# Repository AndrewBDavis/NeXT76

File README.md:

NeXT76 Left-Handed Alps Keyboard
=====================
The primary goal of this project was create as PCB and accompanying layered acrylic case to exclusively support NeXT non-adb keycaps and Alps Electric SKCM/SKCL switches.

Supported Layouts
---------------
This keyboard only supports a [modifed NeXT non-adb layout](https://tinyurl.com/mrxz3pk3) with no volume, brightness or arrow keys and a numpad that is moved to the left of the alphanumericals. Shift key leds are supported.

Numpad Layouts supported:  
| 1u | 1u | 1u | 1u |  | 1u | 1u | 1u | 1u |  | 1u | 1u | 1u | 1u |
|----|----|----|----|--|----|----|----|----|--|----|----|----|----|
| 1u | 1u | 1u | 1u |  | 1u | 1u | 1u | 1u |  | 1u | 1u | 1u | 1u |
| 1u | 1u | 1u | 1u |  | 1u | 1u | 1u | 1u |  | 1u | 1u | 1u | 1u |
| 1u | 1u | 1u | 2u |  | 2u | 1u | 1u | 1u |  | 1u | 1u | 1u | 1u |
| 2u | 2u | 1u | 2u |  | 2u | 1u | 2u | 2u |  | 1u | 2u | 2u | 1u |  

(Some layouts not shown explicitly)

BOM for Alps76 keyboard                                                  
------------------
| REF:  | VALUE:     | FOOTPRINT:           | COMPONENT            |
|------ | ---------- | -------------------- | -------------------- |  
| C1    | 22p        | C_0805               |                      |
| C2    | 22p        | C_0805               |                      |     
| C3    | 1u         | C_0805               |                      |
| C4    | 4.7u       | C_0805               |                      |
| C5    | 0.1u       | C_0805               |                      |
| C6    | 0.1u       | C_0805               |                      |
| C7    | 0.1u       | C_0805               |                      |
| C8    | 0.1u       | C_0805               |                      |
| J1    | USB_mini_B | USB_miniB_hirose_5S8 | UX60SC-MB-5S8 Hirose |
| R1    | 22         | R_0805               |                      |
| R2    | 22         | R_0805               |                      |
| R3    | 10K        | R_0805               |                      |
| R4    | 10K        | R_0805               |                      |
| R5    | 1K         | R_0805               |                      |
| R6    | 1K         | R_0805               |                      |
| R7    | 1K         | R_0805               |                      |
| SW1   | SW_PUSH    | Custom               | TE 1825966-1         |
| U1    | ATMEGA32U4 | QFP44                | ATMega32u4-AU        | 
| X1    | CRYSTAL    | FA-238               | 16MHz, 12PF          |
| D(78) | DIODE      | SOD-123              | 1N4148               |
| LED(3)| LED        | LED_D3.0mm           | 3mm Round Top LED    |

Revisions
-------------
V0.0: 	Prototype  
V1.0: 	Initial Release  
&emsp;&emsp;&nbsp;&nbsp;Cleaned up trace routing  
&emsp;&emsp;&nbsp;&nbsp;Added more numpad configurations  
V1.1: 	Added second numpad LED location option  
V1.2: 	Updated diode footprints,

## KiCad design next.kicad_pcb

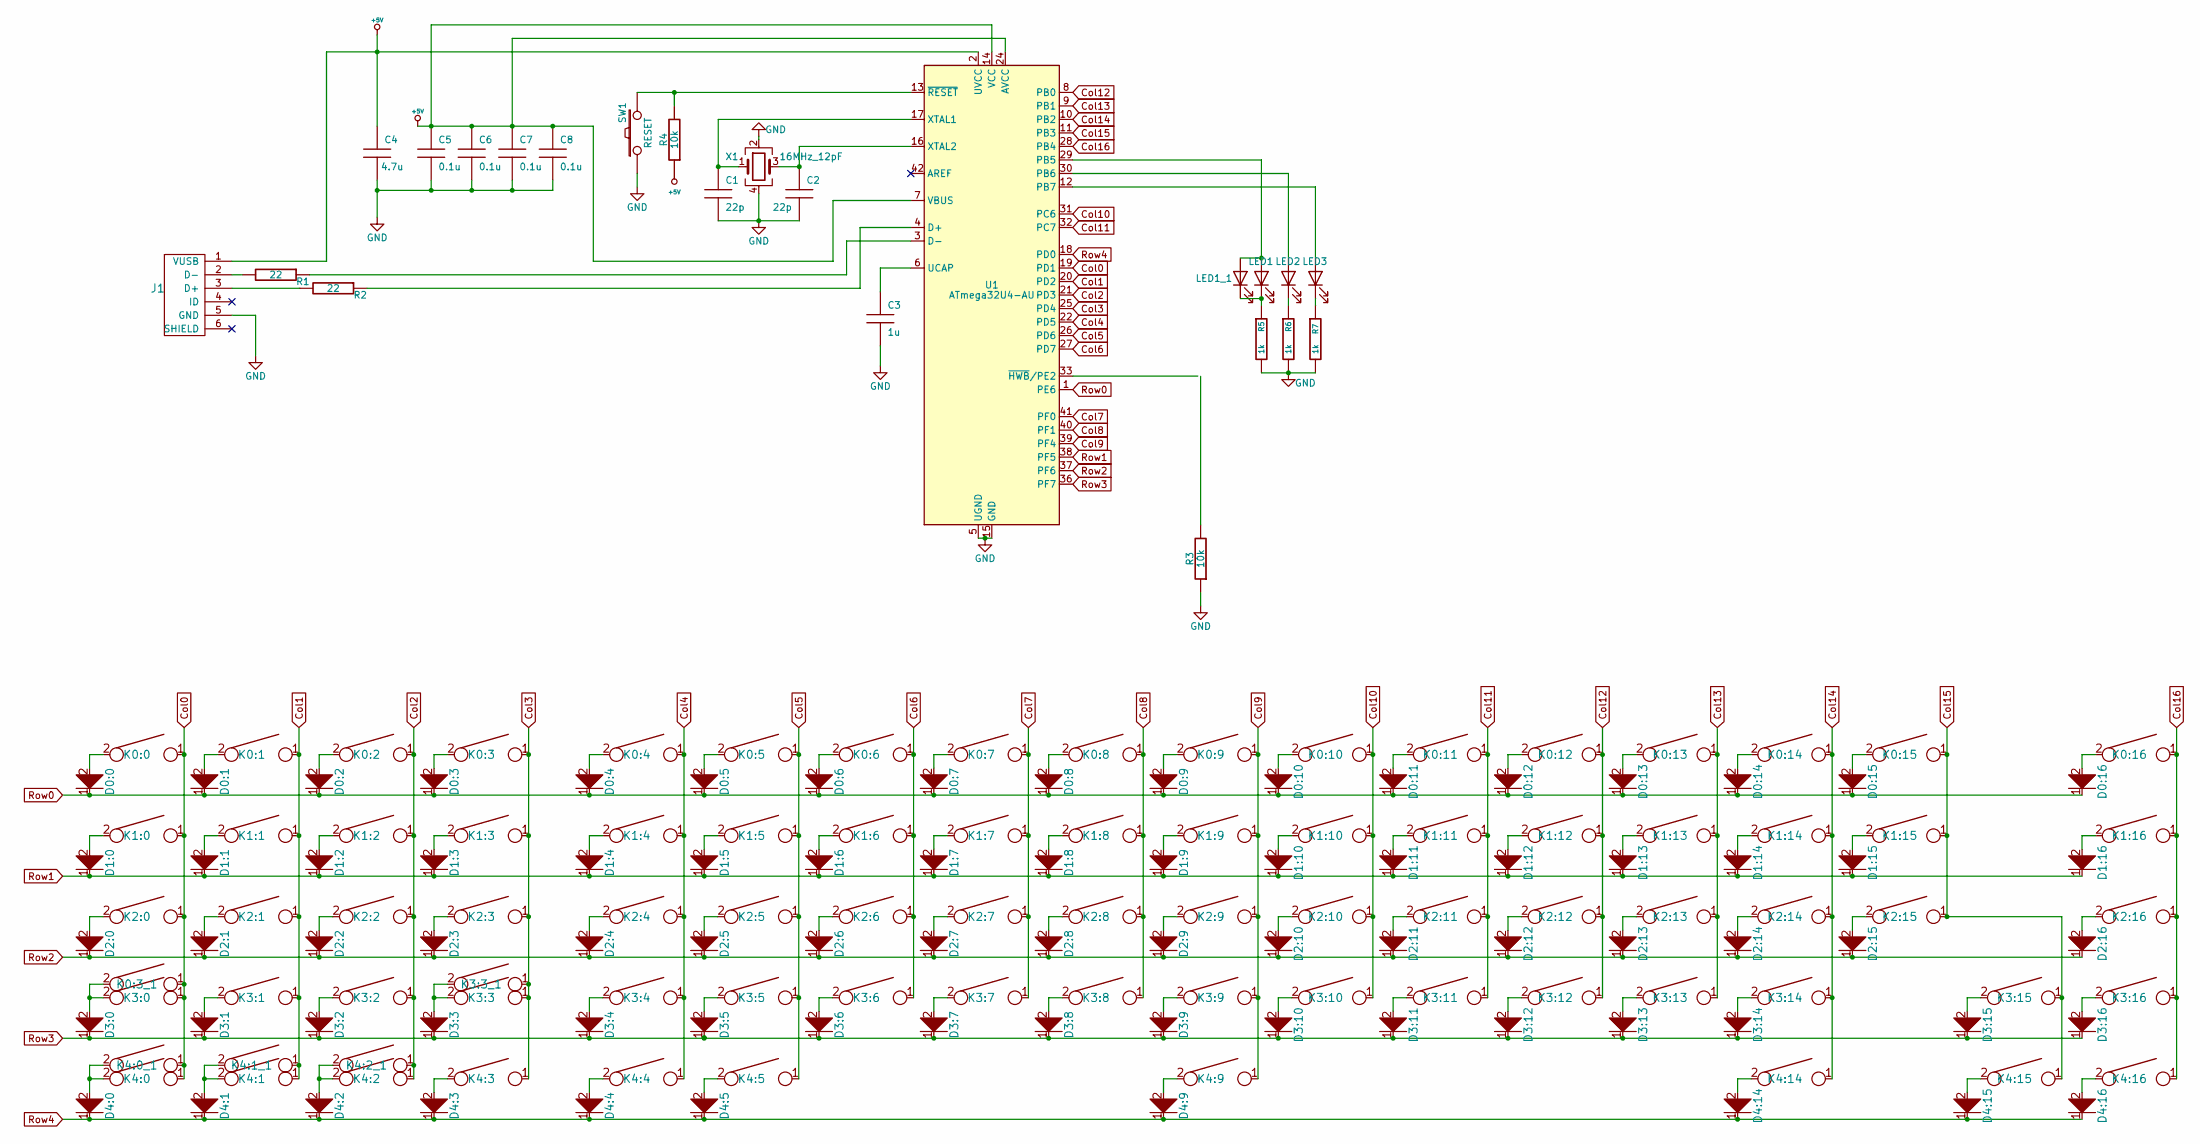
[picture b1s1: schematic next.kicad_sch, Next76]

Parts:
C1, C2: 22p; C_0805_2012Metric
C3: 1u; C_0805_2012Metric
C4: 4.7u; C_0805_2012Metric
C5, C6, C7, C8: 0.1u; C_0805_2012Metric
D0:0, D0:1, D0:2, D0:3, D0:4, D0:5, D0:6, D0:7, D0:8, D0:9, D0:10, D0:11, D0:12, D0:13, D0:14, D0:15, D0:16, D1:0, D1:1, D1:2, D1:3, D1:4, D1:5, D1:6, D1:7, D1:8, D1:9, D1:10, D1:11, D1:12, D1:13, D1:14, D1:15, D1:16, D2:0, D2:1, D2:2, D2:3, D2:4, D2:5, D2:6, D2:7, D2:8, D2:9, D2:10, D2:11, D2:12, D2:13, D2:14, D2:15, D2:16, D3:0, D3:1, D3:2, D3:3, D3:4, D3:5, D3:6, D3:7, D3:8, D3:9, D3:10, D3:11, D3:12, D3:13, D3:14, D3:15, D3:16, D4:0, D4:1, D4:2, D4:3, D4:4, D4:5, D4:9, D4:14, D4:15, D4:16: D; D_SOD-123
J1: USB_mini_micro_B; USB_miniB_hirose_5S8
K0:0, K0:1, K0:2, K0:3, K0:4, K0:5, K0:6, K0:7, K0:8, K0:9, K0:10, K0:11, K0:12, K0:13, K0:14, K0:15, K0:16, K1:0, K1:1, K1:2, K1:3, K1:4, K1:5, K1:6, K1:7, K1:8, K1:9, K1:10, K1:11, K1:12, K1:13, K1:14, K1:15, K1:16, K2:0, K2:1, K2:2, K2:3, K2:4, K2:5, K2:6, K2:7, K2:8, K2:9, K2:10, K2:11, K2:12, K2:13, K2:14, K2:15, K2:16, K3:0, K3:1, K3:2, K3:3, K3:4, K3:5, K3:6, K3:7, K3:8, K3:9, K3:10, K3:11, K3:12, K3:13, K3:14, K3:15, K3:16, K4:0, K4:1, K4:2, K4:3, K4:4, K4:5, K4:9, K4:14, K4:15, K4:16: KEYSW; Alps
K0:3_1, K3:3_1, K4:0_1, K4:1_1, K4:2_1: KEYSW; Alps_Secondary
LED1, LED1_1, LED2, LED3: LED; LED_D3.0mm
R1, R2: 22; R_0805_2012Metric
R3, R4: 10k; R_0805_2012Metric
R5, R6, R7: 1k; R_0805_2012Metric
SW1: RESET; TE_1825966-1
U1: ATmega32U4-AU; LQFP-44_10x10mm_P0.8mm
X1: 16MHz_12pF; Crystal_SMD_SeikoEpson_FA238-4Pin_3.2x2.5mm

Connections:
+5V: C4.1, C5.1, C6.1, C7.1, C8.1, J1.1 (VUSB), R4.1, U1.2 (UVCC), U1.7 (VBUS), U1.14 (VCC), U1.24 (AVCC), U1.34 (VCC), U1.44 (AVCC)
Col0: K0:0.1, K0:3_1.1, K1:0.1, K2:0.1, K3:0.1, K4:0.1, K4:0_1.1, U1.19 (PD1)
Col1: K0:1.1, K1:1.1, K2:1.1, K3:1.1, K4:1.1, K4:1_1.1, U1.20 (PD2)
Col2: K0:2.1, K1:2.1, K2:2.1, K3:2.1, K4:2.1, K4:2_1.1, U1.21 (PD3)
Col3: K0:3.1, K1:3.1, K2:3.1, K3:3.1, K3:3_1.1, K4:3.1, U1.25 (PD4)
Col4: K0:4.1, K1:4.1, K2:4.1, K3:4.1, K4:4.1, U1.22 (PD5)
Col5: K0:5.1, K1:5.1, K2:5.1, K3:5.1, K4:5.1, U1.26 (PD6)
Col6: K0:6.1, K1:6.1, K2:6.1, K3:6.1, U1.27 (PD7)
Col7: K0:7.1, K1:7.1, K2:7.1, K3:7.1, U1.41 (PF0)
Col8: K0:8.1, K1:8.1, K2:8.1, K3:8.1, U1.40 (PF1)
Col9: K0:9.1, K1:9.1, K2:9.1, K3:9.1, K4:9.1, U1.39 (PF4)
Col10: K0:10.1, K1:10.1, K2:10.1, K3:10.1, U1.31 (PC6)
Col11: K0:11.1, K1:11.1, K2:11.1, K3:11.1, U1.32 (PC7)
Col12: K0:12.1, K1:12.1, K2:12.1, K3:12.1, U1.8 (PB0)
Col13: K0:13.1, K1:13.1, K2:13.1, K3:13.1, U1.9 (PB1)
Col14: K0:14.1, K1:14.1, K2:14.1, K3:14.1, K4:14.1, U1.10 (PB2)
Col15: K0:15.1, K1:15.1, K2:15.1, K3:15.1, K4:15.1, U1.11 (PB3)
Col16: K0:16.1, K1:16.1, K2:16.1, K3:16.1, K4:16.1, U1.28 (PB4)
GND: C1.2, C2.2, C3.2, C4.2, C5.2, C6.2, C7.2, C8.2, J1.5 (GND), R3.1, R5.2, R6.2, R7.2, SW1.1, U1.5 (UGND), U1.15 (GND), U1.23 (GND), U1.35 (GND), U1.43 (GND), X1.2, X1.4
unnamed: C1.1, U1.17 (XTAL1), X1.1
unnamed: C2.1, U1.16 (XTAL2), X1.3
unnamed: C3.1, U1.6 (UCAP)
unnamed: D0:0.2, K0:0.2
unnamed: D0:1.2, K0:1.2
unnamed: D0:2.2, K0:2.2
unnamed: D0:3.2, K0:3.2
unnamed: D0:4.2, K0:4.2
unnamed: D0:5.2, K0:5.2
unnamed: D0:6.2, K0:6.2
unnamed: D0:7.2, K0:7.2
unnamed: D0:8.2, K0:8.2
unnamed: D0:9.2, K0:9.2
unnamed: D0:10.2, K0:10.2
unnamed: D0:11.2, K0:11.2
unnamed: D0:12.2, K0:12.2
unnamed: D0:13.2, K0:13.2
unnamed: D0:14.2, K0:14.2
unnamed: D0:15.2, K0:15.2
unnamed: D0:16.2, K0:16.2
unnamed: D1:0.2, K1:0.2
unnamed: D1:1.2, K1:1.2
unnamed: D1:2.2, K1:2.2
unnamed: D1:3.2, K1:3.2
unnamed: D1:4.2, K1:4.2
unnamed: D1:5.2, K1:5.2
unnamed: D1:6.2, K1:6.2
unnamed: D1:7.2, K1:7.2
unnamed: D1:8.2, K1:8.2
unnamed: D1:9.2, K1:9.2
unnamed: D1:10.2, K1:10.2
unnamed: D1:11.2, K1:11.2
unnamed: D1:12.2, K1:12.2
unnamed: D1:13.2, K1:13.2
unnamed: D1:14.2, K1:14.2
unnamed: D1:15.2, K1:15.2
unnamed: D1:16.2, K1:16.2
unnamed: D2:0.2, K2:0.2
unnamed: D2:1.2, K2:1.2
unnamed: D2:2.2, K2:2.2
unnamed: D2:3.2, K2:3.2
unnamed: D2:4.2, K2:4.2
unnamed: D2:5.2, K2:5.2
unnamed: D2:6.2, K2:6.2
unnamed: D2:7.2, K2:7.2
unnamed: D2:8.2, K2:8.2
unnamed: D2:9.2, K2:9.2
unnamed: D2:10.2, K2:10.2
unnamed: D2:11.2, K2:11.2
unnamed: D2:12.2, K2:12.2
unnamed: D2:13.2, K2:13.2
unnamed: D2:14.2, K2:14.2
unnamed: D2:15.2, K2:15.2
unnamed: D2:16.2, K2:16.2
unnamed: D3:0.2, K0:3_1.2, K3:0.2
unnamed: D3:1.2, K3:1.2
unnamed: D3:2.2, K3:2.2
unnamed: D3:3.2, K3:3.2, K3:3_1.2
unnamed: D3:4.2, K3:4.2
unnamed: D3:5.2, K3:5.2
unnamed: D3:6.2, K3:6.2
unnamed: D3:7.2, K3:7.2
unnamed: D3:8.2, K3:8.2
unnamed: D3:9.2, K3:9.2
unnamed: D3:10.2, K3:10.2
unnamed: D3:11.2, K3:11.2
unnamed: D3:12.2, K3:12.2
unnamed: D3:13.2, K3:13.2
unnamed: D3:14.2, K3:14.2
unnamed: D3:15.2, K3:15.2
unnamed: D3:16.2, K3:16.2
unnamed: D4:0.2, K4:0.2, K4:0_1.2
unnamed: D4:1.2, K4:1.2, K4:1_1.2
unnamed: D4:2.2, K4:2.2, K4:2_1.2
unnamed: D4:3.2, K4:3.2
unnamed: D4:4.2, K4:4.2
unnamed: D4:5.2, K4:5.2
unnamed: D4:9.2, K4:9.2
unnamed: D4:14.2, K4:14.2
unnamed: D4:15.2, K4:15.2
unnamed: D4:16.2, K4:16.2
unnamed: J1.2 (D-), R1.2
unnamed: J1.3 (D+), R2.2
unnamed: LED1.1 (K), LED1_1.1 (K), R5.1
unnamed: LED1.2 (A), LED1_1.2 (A), U1.29 (PB5)
unnamed: LED2.1 (K), R6.1
unnamed: LED2.2 (A), U1.30 (PB6)
unnamed: LED3.1 (K), R7.1
unnamed: LED3.2 (A), U1.12 (PB7)
unnamed: R1.1, U1.3 (D-)
unnamed: R2.1, U1.4 (D+)
unnamed: R3.2, U1.33 (~HWB/PE2)
unnamed: R4.2, SW1.2, U1.13 (~RESET)
Row0: D0:0.1, D0:1.1, D0:2.1, D0:3.1, D0:4.1, D0:5.1, D0:6.1, D0:7.1, D0:8.1, D0:9.1, D0:10.1, D0:11.1, D0:12.1, D0:13.1, D0:14.1, D0:15.1, D0:16.1, U1.1 (PE6)
Row1: D1:0.1, D1:1.1, D1:2.1, D1:3.1, D1:4.1, D1:5.1, D1:6.1, D1:7.1, D1:8.1, D1:9.1, D1:10.1, D1:11.1, D1:12.1, D1:13.1, D1:14.1, D1:15.1, D1:16.1, U1.38 (PF5)
Row2: D2:0.1, D2:1.1, D2:2.1, D2:3.1, D2:4.1, D2:5.1, D2:6.1, D2:7.1, D2:8.1, D2:9.1, D2:10.1, D2:11.1, D2:12.1, D2:13.1, D2:14.1, D2:15.1, D2:16.1, U1.37 (PF6)
Row3: D3:0.1, D3:1.1, D3:2.1, D3:3.1, D3:4.1, D3:5.1, D3:6.1, D3:7.1, D3:8.1, D3:9.1, D3:10.1, D3:11.1, D3:12.1, D3:13.1, D3:14.1, D3:15.1, D3:16.1, U1.36 (PF7)
Row4: D4:0.1, D4:1.1, D4:2.1, D4:3.1, D4:4.1, D4:5.1, D4:9.1, D4:14.1, D4:15.1, D4:16.1, U1.18 (PD0)

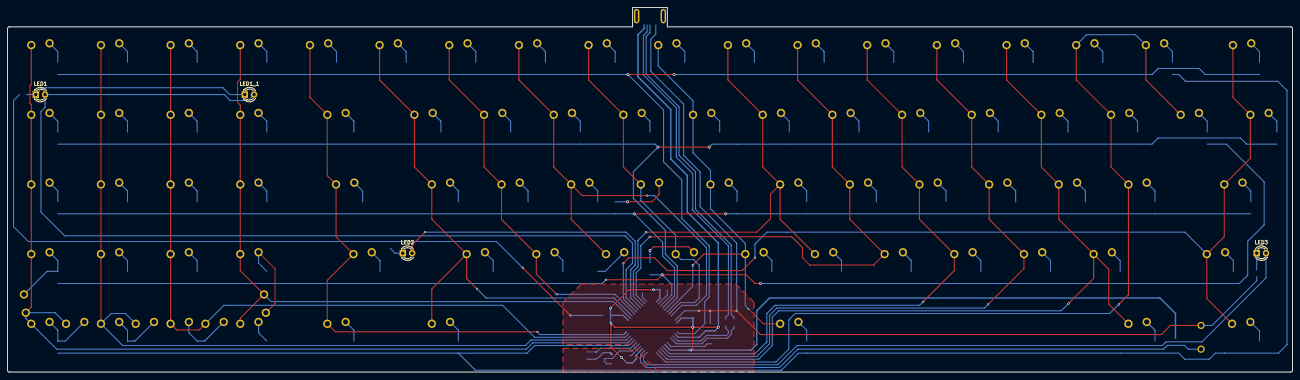
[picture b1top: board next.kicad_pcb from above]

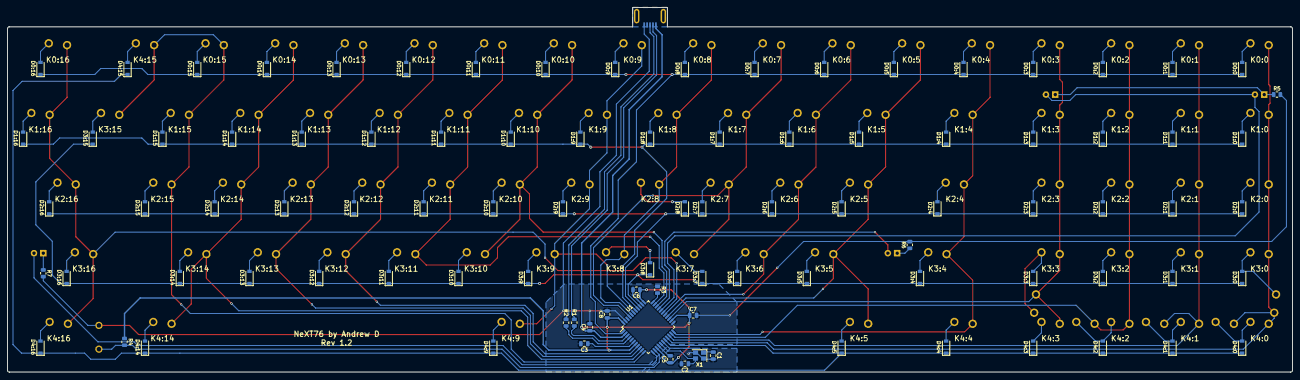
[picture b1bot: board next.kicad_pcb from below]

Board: 2 copper layers, 351.4 x 99.7 mm, 184 parts (97 on the bottom side), 117 nets.

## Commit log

2022-03-14 Updated Model
2022-03-14 Update Model
2022-03-15 Numpad Config Changed
2022-03-15 Update Picture
2022-03-18 Update Axial_Diode Footprint
2022-03-23 Added LED opttion
2022-03-23 Update diodes
2022-03-24 Extend USB port mount
2022-03-25 Adjust USB port
